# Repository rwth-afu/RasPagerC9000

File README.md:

# RasPagerC9000
Adapted Version of RasPager to generate Signals for Ericsson C9000 Paging Transmitter

Authors:
* Ralf Wilke DH3WR, Aachen
* Michael Delissen, Aachen
* Marvin Menzerath, Aachen
* Christian Jansen, Aachen
* Philipp Thiel, Aachen
* Thomas Gatzweiler

This software is released free of charge under the Creative Commons License of type "by-nc-sa". No commercial use is allowed. The software licenses of the used libs apply in any case.

Please notice that there is a new software development without the need of java and with web frontend. Check out https://github.com/rwth-afu/UniPager

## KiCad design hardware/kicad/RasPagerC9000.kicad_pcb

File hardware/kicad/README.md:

# KiCad hardware

This is an electrically identical remake of the original board.

> [!CAUTION]  
> This board is untested; the warning will be removed once functionality is confirmed.

[Schematic](RasPagerC9000.pdf)

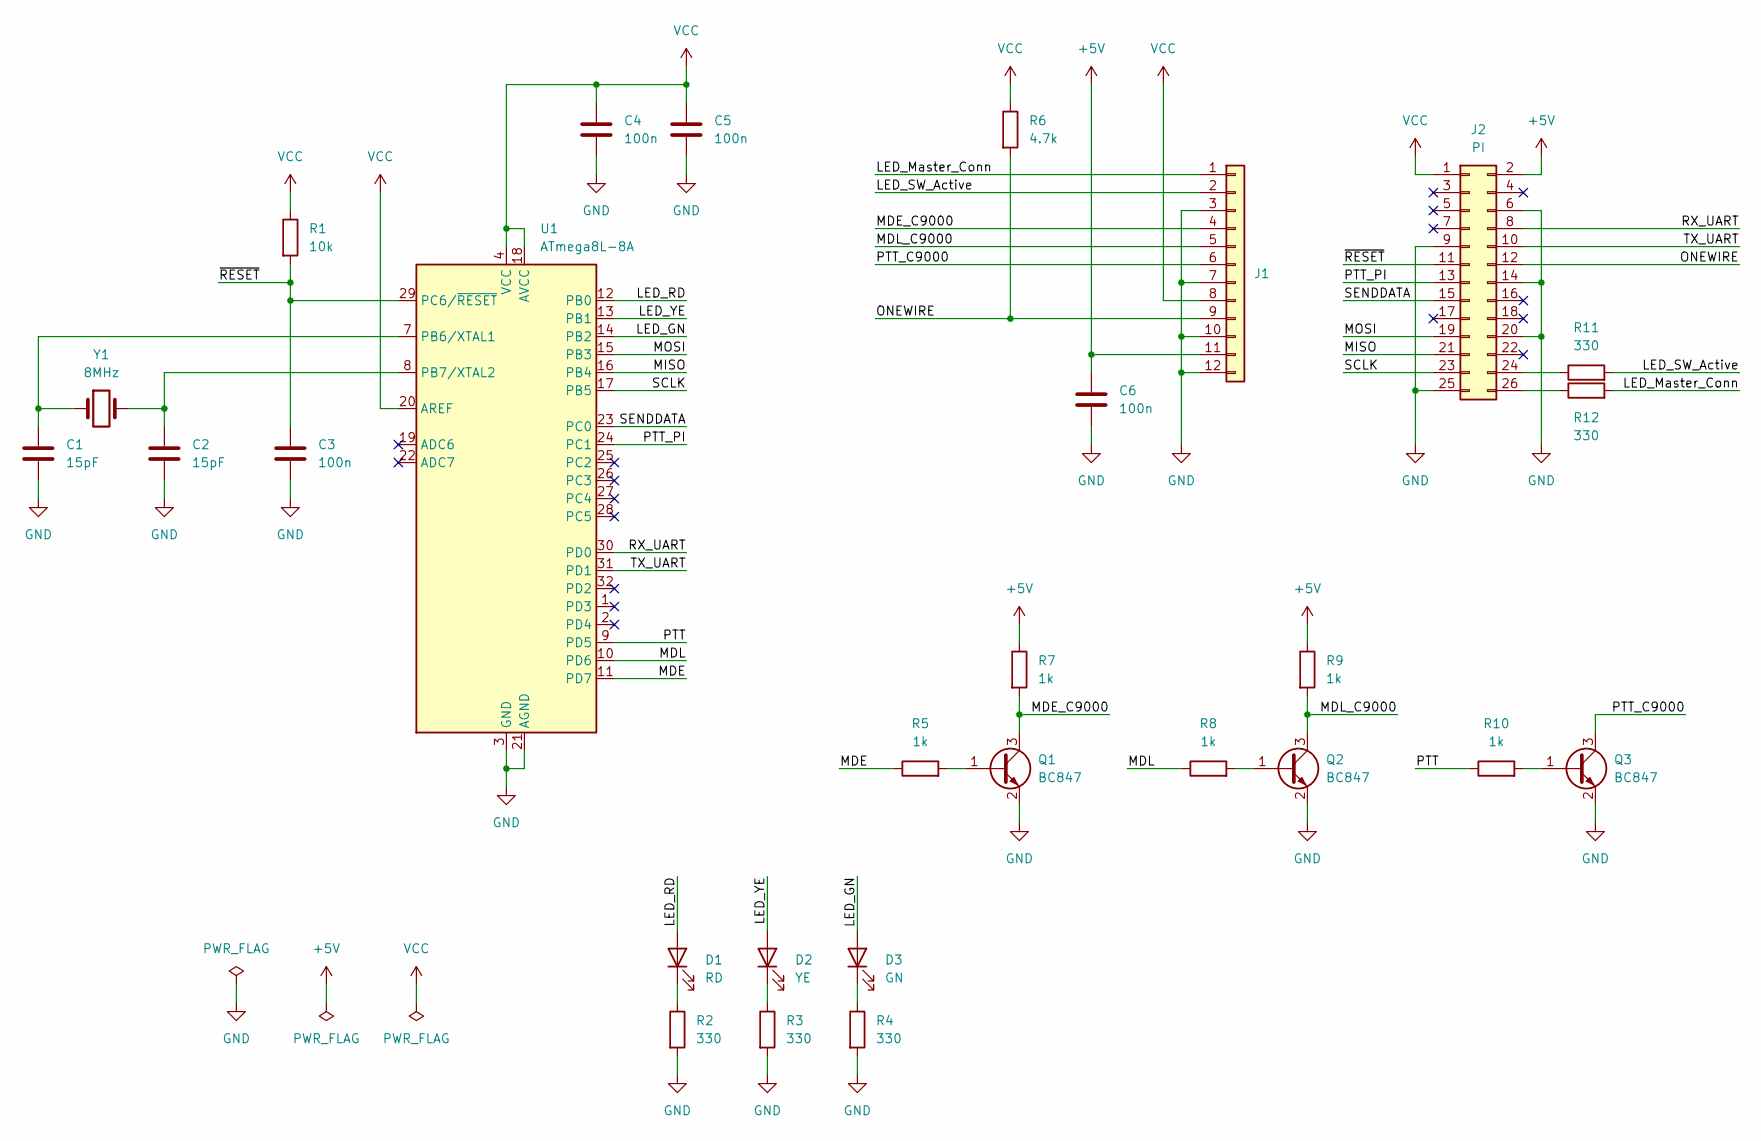
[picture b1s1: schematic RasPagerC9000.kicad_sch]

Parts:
C1, C2: 15pF; C_0603_1608Metric; LCSC C1644
C3, C4, C5, C6: 100n; C_0603_1608Metric; LCSC C14663
D1: RD; LED_0805_2012Metric; LCSC C2295
D2: YE; LED_0805_2012Metric; LCSC C2296
D3: GN; LED_0805_2012Metric; LCSC C2297
J1: Conn_01x12; PinHeader_1x12_P2.54mm_Vertical; LCSC C6332195
J2: PI; PinSocket_2x13_P2.54mm_Vertical; LCSC C25503126
Q1, Q2, Q3: BC847; SOT-23; LCSC C8664
R1: 10k; R_0603_1608Metric; LCSC C25804
R2, R3, R4, R11, R12: 330; R_0603_1608Metric; LCSC C23138
R5, R7, R8, R9, R10: 1k; R_0603_1608Metric; LCSC C21190
R6: 4.7k; R_0603_1608Metric; LCSC C23162
U1: ATmega8L-8A; TQFP-32_7x7mm_P0.8mm; LCSC C9755
Y1: 8MHz; Crystal_SMD_HC49-SD; LCSC C12674

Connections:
+5V: C6.1, J1.11, J2.2, R7.1, R9.1
/LED_GN: D3.2 (A), U1.14 (PB2)
/LED_Master_Conn: J1.1, R12.2
/LED_RD: D1.2 (A), U1.12 (PB0)
/LED_SW_Active: J1.2, R11.2
/LED_YE: D2.2 (A), U1.13 (PB1)
/MDE: R5.1, U1.11 (PD7)
/MDE_C9000: J1.4, Q1.3 (C), R7.2
/MDL: R8.1, U1.10 (PD6)
/MDL_C9000: J1.5, Q2.3 (C), R9.2
/MISO: J2.21, U1.16 (PB4)
/MOSI: J2.19, U1.15 (PB3)
/ONEWIRE: J1.9, J2.12, R6.2
/PTT: R10.1, U1.9 (PD5)
/PTT_C9000: J1.6, Q3.3 (C)
/PTT_PI: J2.13, U1.24 (PC1)
/RX_UART: J2.8, U1.30 (PD0)
/SCLK: J2.23, U1.17 (PB5)
/SENDDATA: J2.15, U1.23 (PC0)
/TX_UART: J2.10, U1.31 (PD1)
/~RESET: C3.1, J2.11, R1.2, U1.29 (PC6/~RESET)
GND: C1.2, C2.2, C3.2, C4.2, C5.2, C6.2, J1.3, J1.7, J1.10, J1.12, J2.6, J2.9, J2.14, J2.20, J2.25, Q1.2 (E), Q2.2 (E), Q3.2 (E), R2.2, R3.2, R4.2, U1.3 (GND), U1.5 (GND), U1.21 (AGND)
unnamed: D1.1 (K), R2.1
unnamed: D2.1 (K), R3.1
unnamed: D3.1 (K), R4.1
unnamed: J2.24, R11.1
unnamed: J2.26, R12.1
unnamed: Q1.1 (B), R5.2
unnamed: Q2.1 (B), R8.2
unnamed: Q3.1 (B), R10.2
unnamed: C1.1, U1.7 (PB6/XTAL1), Y1.1
unnamed: C2.1, U1.8 (PB7/XTAL2), Y1.2
VCC: C4.1, C5.1, J1.8, J2.1, R1.1, R6.1, U1.4 (VCC), U1.6 (VCC), U1.18 (AVCC), U1.20 (AREF)

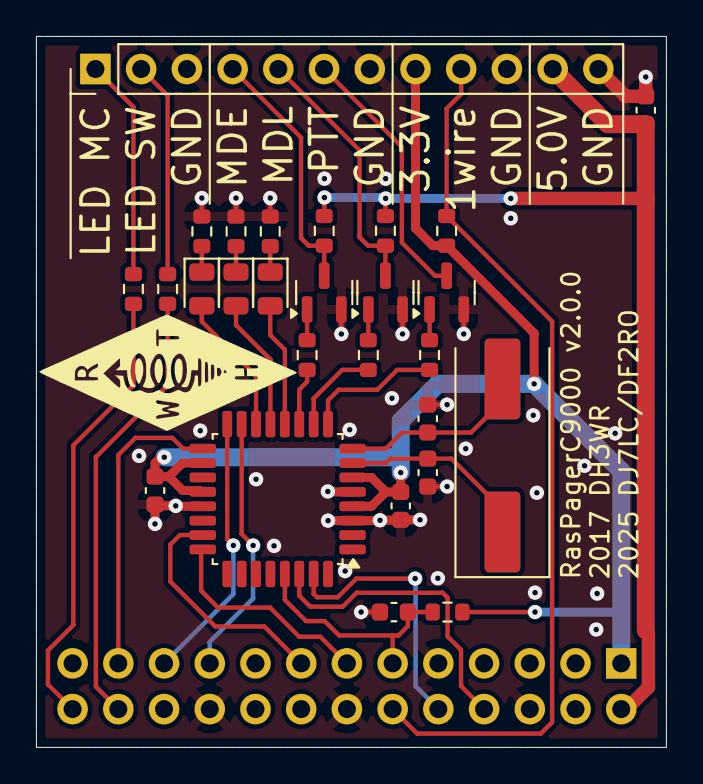
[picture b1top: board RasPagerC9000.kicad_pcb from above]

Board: 2 copper layers, 35.0 x 39.5 mm, 28 parts (1 on the bottom side), 33 nets.

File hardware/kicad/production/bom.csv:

Designator,Footprint,Quantity,Value,LCSC Part #
"C1, C2",0603,2,15pF,C1644
"C3, C4, C5, C6",0603,4,100n,C14663
D1,0805,1,RD,C2295
D2,0805,1,YE,C2296
D3,0805,1,GN,C2297
J1,PinHeader_1x12_P2.54mm_Vertical,1,Conn_01x12,C6332195
J2,PinSocket_2x13_P2.54mm_Vertical,1,PI,C25503126
"Q1, Q2, Q3",SOT-23,3,BC847,C8664
R1,0603,1,10k,C25804
"R10, R5, R7, R8, R9",0603,5,1k,C21190
"R11, R12, R2, R3, R4",0603,5,330,C23138
R6,0603,1,4.7k,C23162
U1,TQFP-32_7x7mm_P0.8mm,1,ATmega8L-8A,C9755
Y1,Crystal_SMD_HC49-SD,1,8MHz,C12674

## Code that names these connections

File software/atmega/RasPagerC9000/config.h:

// Frequency
#define F_CPU 8000000

// LED_RED -> This pin drives the red LED
#define LED_RED_PORT      PORTB
#define LED_RED_PIN       PINB
#define LED_RED_BIT       PINB0

// LED_YELLOW -> This pin drives the yellow LED
#define LED_YELLOW_PORT      PORTB
#define LED_YELLOW_PIN       PINB
#define LED_YELLOW_BIT       PINB1

// LED_GREEN -> This pin drives the green LED
#define LED_GREEN_PORT      PORTB
#define LED_GREEN_PIN       PINB
#define LED_GREEN_BIT       PINB2

// PTT_C9000 -> This pin drives the PTT line of C9000, High means C9000 is set to Ground = Low
#define PTT_C9000_PORT      PORTD
#define PTT_C9000_PIN       PIND
#define PTT_C9000_BIT       PIND5

// MDL_C9000 -> This pin drives the MDL line of C9000, High means C9000 MDL is set to Ground = Low
#define MDL_C9000_PORT      PORTD
#define MDL_C9000_PIN       PIND
#define MDL_C9000_BIT       PIND6

// MDE_C9000 -> This pin drives the MDE line of C9000, High means C9000 MDL is set to Ground = Low
#define MDE_C9000_PORT      PORTD
#define MDE_C9000_PIN       PIND
#define MDE_C9000_BIT       PIND7

// RASPI_SENDATA -> This pin drives the MDE line of C9000, High means C9000 MDL is set to Ground = Low
#define RASPI_SENDATA_PORT      PORTC
#define RASPI_SENDATA_PIN       PINC
#define RASPI_SENDATA_BIT       PINC0

// RASPI_PTT -> This pin drives the MDE line of C9000, High means C9000 MDL is set to Ground = Low
#define RASPI_PTT_PORT      PORTC
#define RASPI_PTT_PIN       PINC
#define RASPI_PTT_BIT       PINC1

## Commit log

2016-10-19 Initial commit of hardware
2016-10-19 Kommunikation Java <-> ATMega definiert
2016-10-26 Wider pads for GPIO header
2016-10-26 Added PCB printout
2016-10-27 Add Makefile and avrdude.conf
2016-10-28 Changed XTAL Frequency from 12 MHz to 8 MHz, added part placement drawing
2016-10-28 Changed the java ATMega communication to be more understandable
2016-10-28 Added first starting point code for ATmega and Atmel Studio 7.0 project files
2016-10-28 Added directory for java program
2016-10-28 Update README.md
    Added some authorship comments
2016-10-28 Initial atmega8 firmware implementation
2016-10-31 Added Run & Build instructions
2016-10-31 Added first version of Java-software
2016-11-01 Improve names and descriptions in config.h
2016-11-01 Implement C9000 MDE signal and status LED outputs
2016-11-01 Add a README on how to flash the atmega firmware
2016-11-02 Moved Java documentation into seperate README.md
2016-11-02 Moved Java application to IntelliJ IDEA project
2016-11-02 Bulk code formatting
2016-11-02 Added baudrate to configfile and README (#1)
2016-11-02 Added new JAR file (fix #2)
2016-11-02 More code formatting
2016-11-02 Add recommended baudrates to config.h (close #1)
2016-11-02 Change default baudrate to 38400
2016-11-02 Set GPIO_00 to HIGH on start (#1)
2016-11-02 Added new JAR
2016-11-02 Only start GUI if not in a headless environment
2016-11-02 Add the option to invert data bits to config.h
2016-11-02 More formatting
2016-11-02 Improve thread-safety of Fifo class
2016-11-03 Rename IntelliJ project to 'RasPagerC9000'
2016-11-03 Set MDL pin to LOW as default
2016-11-10 Add IntelliJ codeStyleSettings.xml
2016-11-11 Bugfixing on ATMega Software, now transfer is running as expected and terminating always. Still no RX on Skypers.
2016-11-11 Implement changes from SDRPager (WIP)
2016-11-24 Implement atmega panic function
2016-11-25 Added alarm flashing if an error has happend
2016-11-25 Make writes to FIFO head/tail indices threadsafe
2016-12-19 Update with to master branch of SDR Pager, first try
2016-12-19 added idea dir
2016-12-19 Added pom.xml
2016-12-19 Updated Filename of JAR file in start script
2016-12-19 Code now running, at least with DB6AC Pager, DH3WR & DL5FMK still not working
2016-12-19 Changed line endings to linux
2016-12-19 Added tx delay
2016-12-19 Interrupt freq. of bit output maybe not precise enough, let's try
2016-12-20 Use Timer 1 to generate 1200 Baud Interrupt, now working fine
2016-12-20 Remove of txdelay
2016-12-20 Debugged maxBatch calculation, added better state machine handling of non-complete slots.
2016-12-20 No logging output of received message, now fixed
2016-12-20 Added debug message for max Batches, added differentiation, if slot is complete or not
2016-12-20 Bug Fix: If slot is incomplete but there is not enough time left for even the preamble, dont's encode
2016-12-20 More debugging
2016-12-20 More debugging of scheduler
2016-12-20 Update logging output of several variables
2016-12-20 Fixed Error in getTimeToNextSlot
2016-12-20 Forgotten modulo operator at "time left in this slot"-calculation
2016-12-20 Again "time_to_next_slot", now with Math.floorMod instead of "%", added message.pop debugging
2016-12-21 Nichts für Dumme mit dem Time Left ...
2016-12-21 Es gibt schon einen Unterschied zwischen a%b und floor(a/b)...
2016-12-21 Noch ein Fehler
2016-12-21 letzter Versuch heute
2016-12-21 allerletzter Test
2016-12-21 2...
2016-12-21 Now RC2 is released. Removed debug messages.
2016-12-21 New handshake between Java and ATMega. Now bulk transfers of 40 Bytes
2016-12-21 Adapted Java C9000 Transmitter to new bulk transfer
2016-12-21 Debug of ATMega software
2016-12-21 Syntax error, still not working well with longer calls
2016-12-21 Logic bugfixing with new data transfer method between Pi and ATMega
2016-12-22 Preparations for Version 1.0.0
2017-01-09 Added two side version with one wire-Bus connection
2017-01-09 Added schematic and parts placement info
2017-01-09 Remove serial delay in window
2017-01-09 Update of PI2ATMega Communication
2017-01-09 Rename of file
2017-01-09 Added info about RustPager
2017-01-09 Added RustPager
2017-02-04 Added BOM
2017-02-04 Renamed PDF
2017-02-04 Updating Schematic with author information
2017-02-04 Refactoring of Excel BOM
2017-02-04 Updated BOM with component values that were missing before
2017-07-29 Updated to UniPager
2017-08-19 Added Website template for C9000
2019-11-18 Added php Script with dynamic link IP generation for admin interface
2019-11-18 Bump netty-all in /software/raspager-java
    Bumps [netty-all](https://github.com/netty/netty) from 4.1.6.Final to 4.1.42.Final.
    - [Release notes](https://github.com/netty/netty/releases)
    - [Commits](https://github.com/netty/netty/compare/netty-4.1.6.Final...netty-4.1.42.Final)
2025-07-24 Add gitignore for KiCad 9
2025-07-24 Exclude KiCad board production files in gitignore
    This allows commiting the BOM and positions csv files.
2025-07-24 Add JLCPCB production files for KiCad hardware
    RasPagerC9000_v2.0.0.zip contains the gerber files.
    The archive, bom and positions file can be uploaded directly to JLCPCB.
2025-07-24 Add KiCad project & schematic
    The schematic is electrically identical to the original one.
2025-07-24 Add KiCad PCB layout
2025-07-24 Add KiCad schematic PDF
2025-07-24 KiCad hw: Add readme including PCB rendering
2025-07-24 KiCad HW: Add warning to readme about untested board
